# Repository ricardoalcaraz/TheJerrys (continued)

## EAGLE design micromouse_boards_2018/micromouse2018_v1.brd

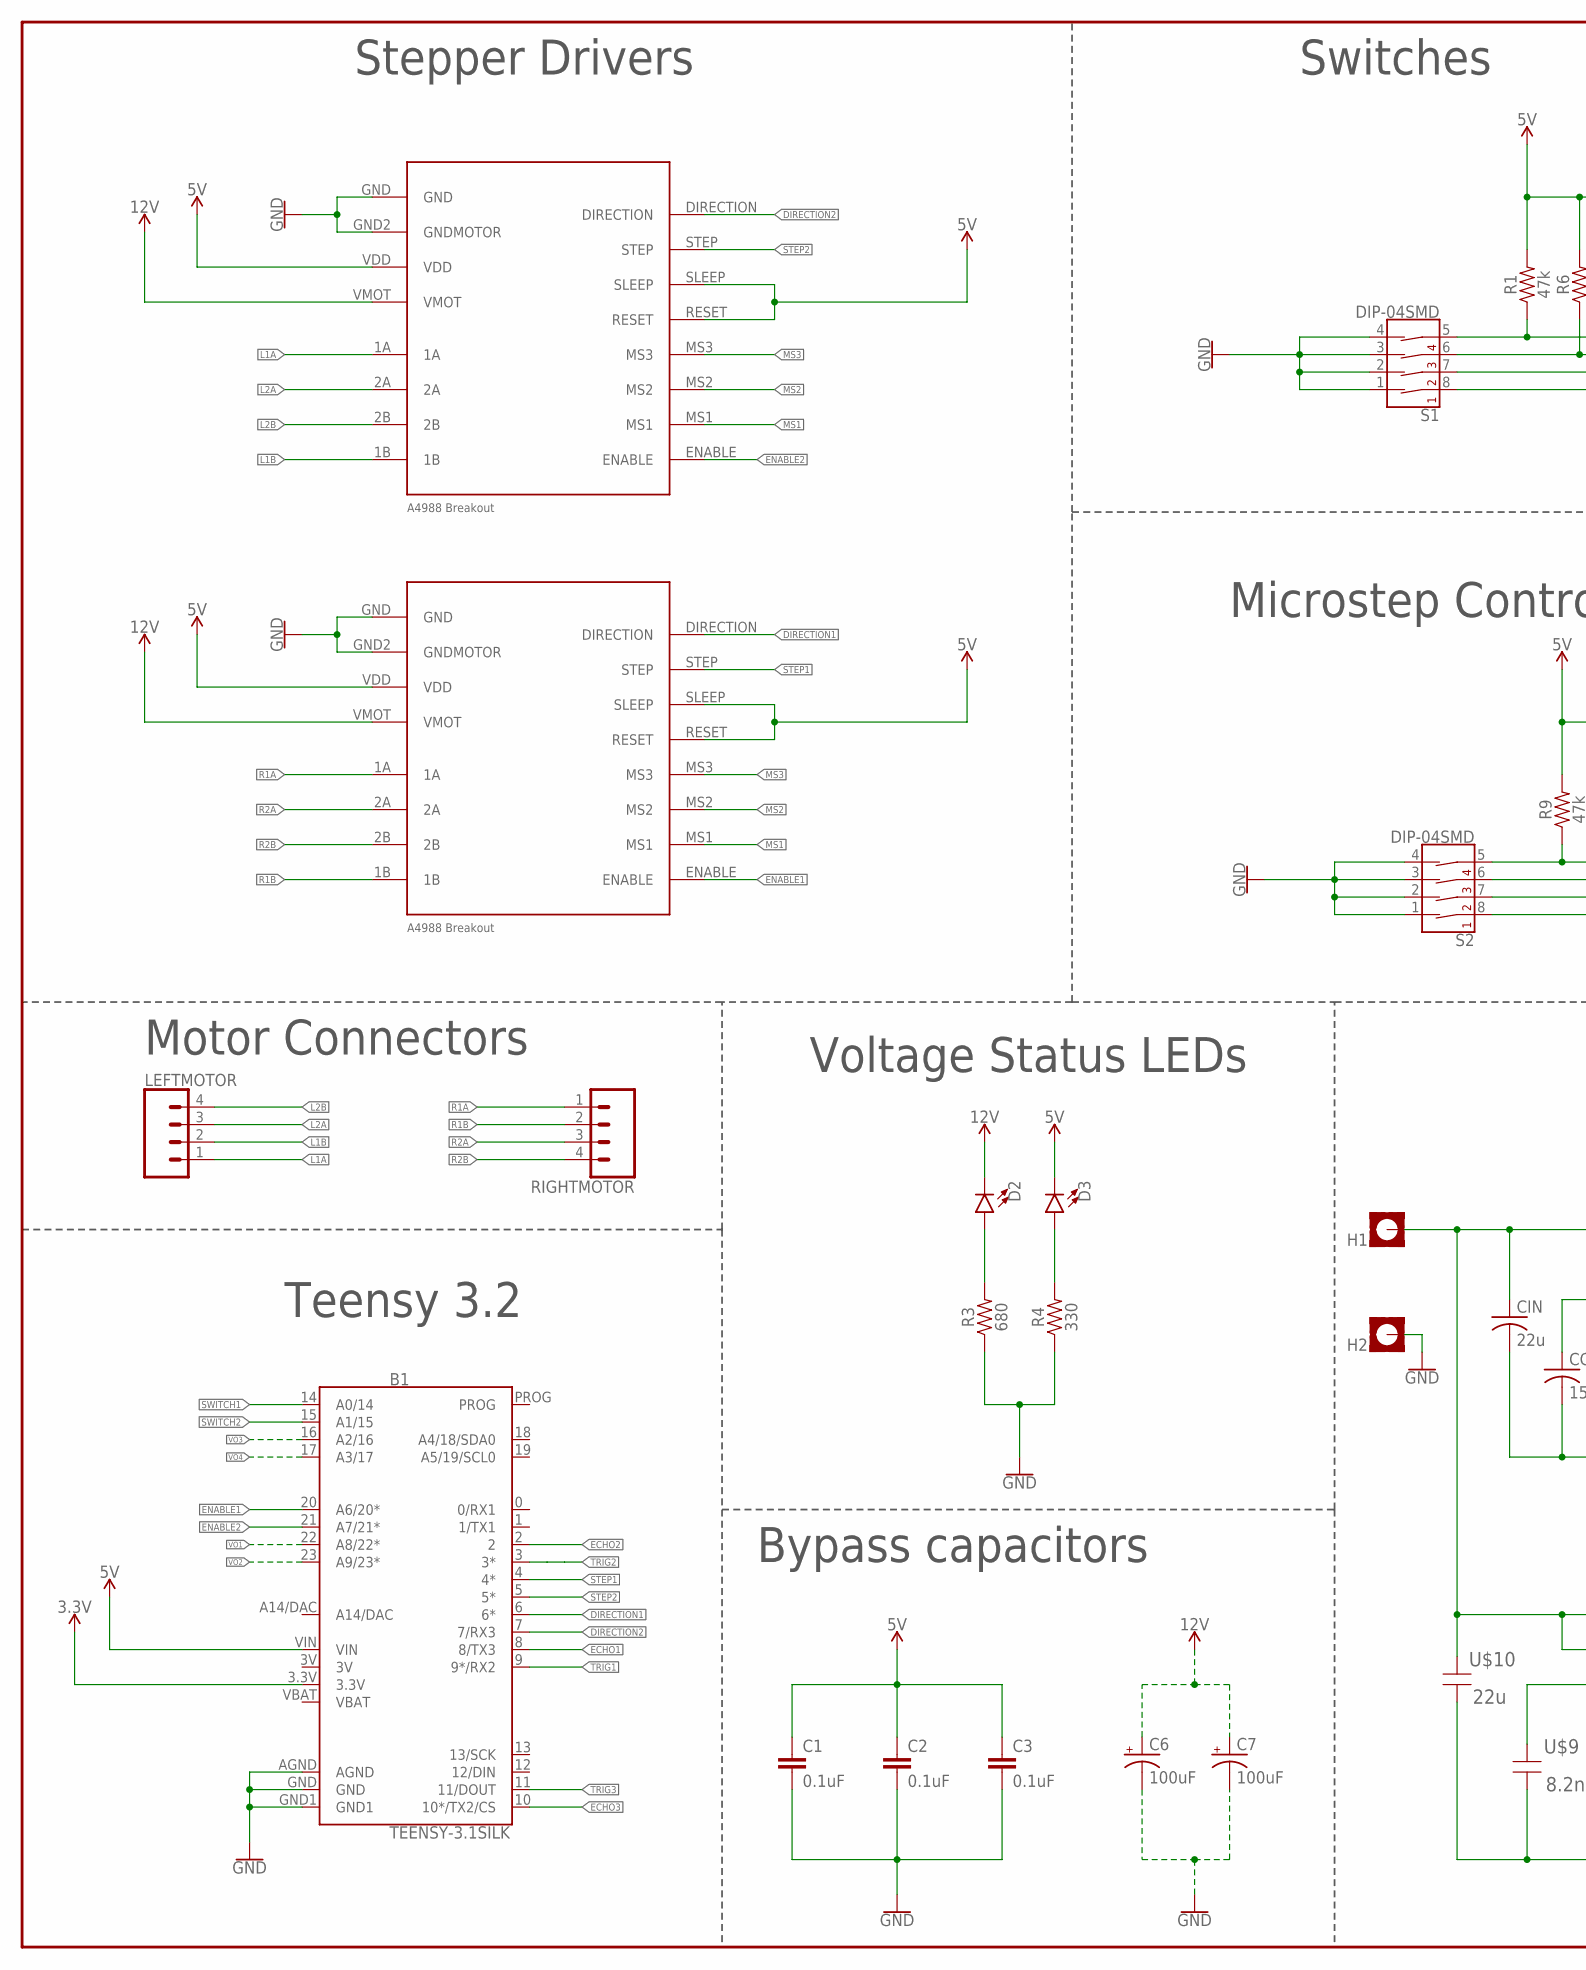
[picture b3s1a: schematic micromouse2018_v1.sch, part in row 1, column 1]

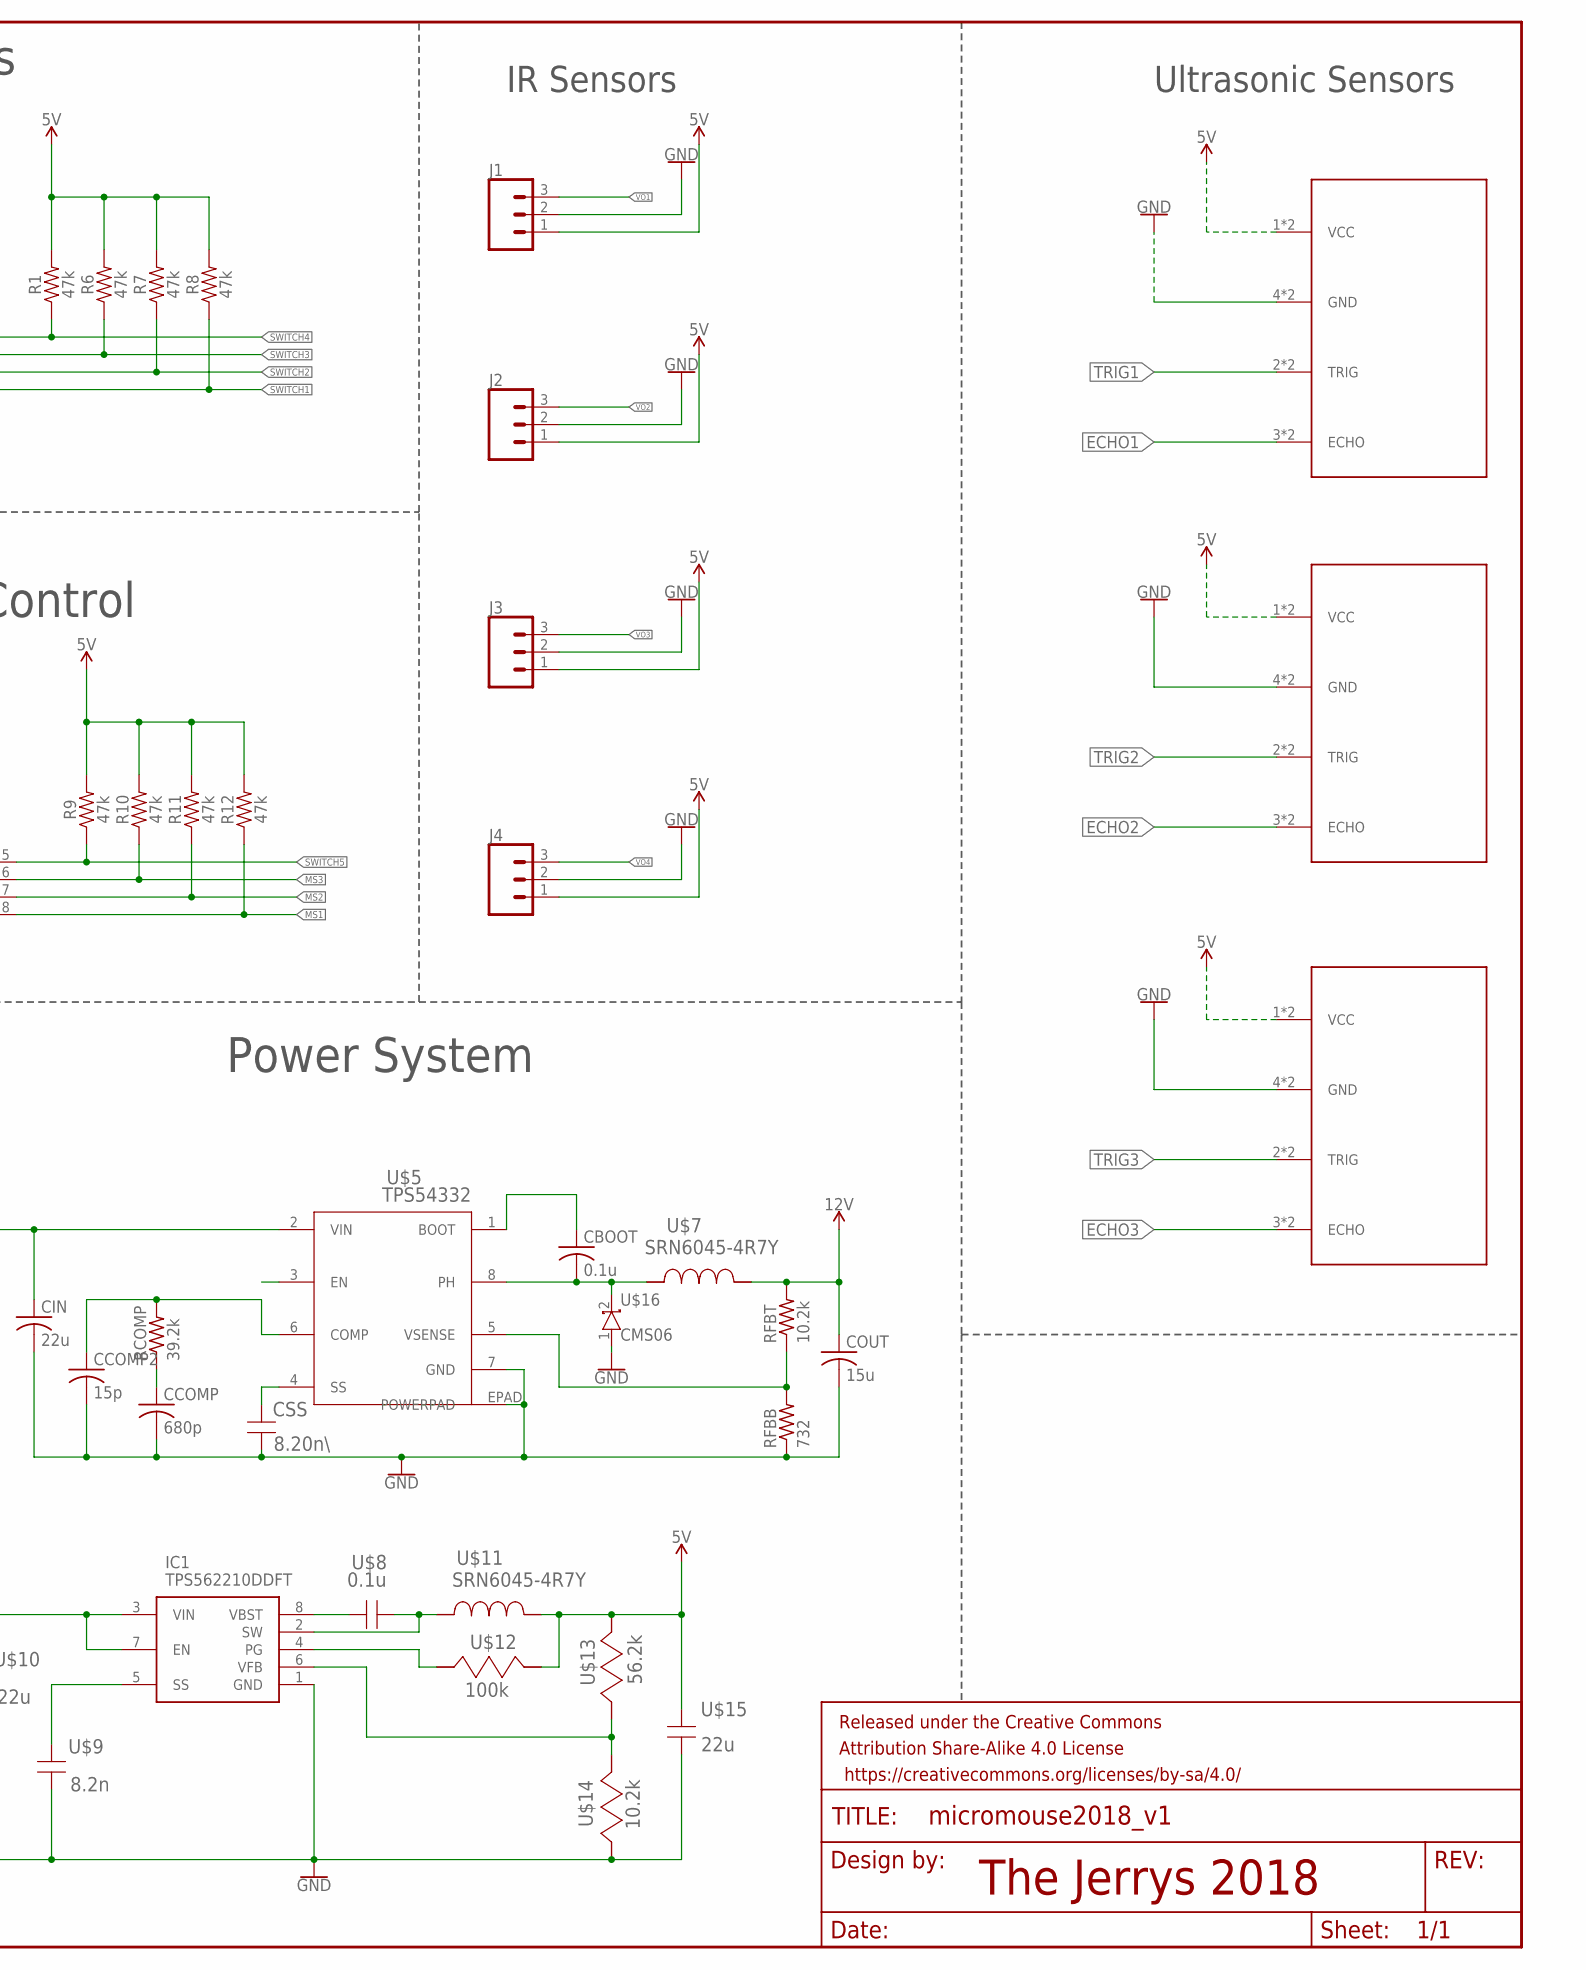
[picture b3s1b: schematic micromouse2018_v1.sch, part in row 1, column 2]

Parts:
B1: TEENSY-3.1SILK; TEENSY-3.1
C1, C2, C3: 0.1uF; 0603
C6, C7: 100uF; PANASONIC_D
CBOOT: 0.1u; C0805
CCOMP: 680p; C0805
CCOMP2: 15p; C0805
CIN: 22u; C1210
COUT: 15u; C0805
CSS: 8.20n\; 1206
D2, D3: LED0603; LED-0603
FRAME1: FRAME-LEDGER; CREATIVE_COMMONS
H1, H2: MOUNT-PAD-SQUARE2.8; 2,8-PAD-SQUARE
IC1: TPS562210DDFT; SOT65P280X110-8N
J1, J2, J3, J4: CONN_03JST-PTH-VERT; JST-3-PTH-VERT
LEFTMOTOR: CONN_04LONGPADS; 1X04_LONGPADS
R1, R6, R7, R8, R9, R10, R11, R12: 47k; 0603
R3: 680; 0603
R4: 330; 0603
RCOMP: 39.2k; R0805
RFBB: 732; R0805
RFBT: 10.2k; R0805
RIGHTMOTOR: CONN_04LONGPADS; 1X04_LONGPADS
S1, S2: DIP-04SMD; DIPSWITCH-04-SMD
U$1, U$2: A4988_BREAKOUT
U$3, U$4, U$6: ULTRASONIC; 1X04_SMD_VERTICAL_COMBO
U$5: TPS54332; DDA8_2P13X3-M
U$7, U$11: SRN6045-4R7Y; SRN6045
U$8: 0.1u; 0805
U$9: 8.2n; 1206
U$10: 22u; 1210
U$12: 100k; 0805
U$13: 56.2k; 0805
U$14: 10.2k; 0805
U$15: 22u; 1206_190
U$16: CMS06; SODFL4724X108N

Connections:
3.3V: B1.3.3V
3V: B1.3V
5V: B1.VIN, C1.1, C2.1, C3.1, D3.C, J1.1, J2.1, J3.1, J4.1, R1.2, R6.2, R7.2, R8.2, R9.2, R10.2, R11.2, R12.2, U$1.RESET, U$1.SLEEP, U$1.VDD, U$2.RESET, U$2.SLEEP, U$2.VDD, U$3.1 (VCC), U$3.1-2 (VCC), U$4.1 (VCC), U$4.1-2 (VCC), U$6.1 (VCC), U$6.1-2 (VCC), U$11.2, U$12.1, U$13.1, U$15.1
12V: C6.+, C7.+, COUT.1, D2.C, RFBT.2, U$1.VMOT, U$2.VMOT, U$7.2
BOOT: IC1.2 (SW), U$8.1, U$11.1
DIRECTION1: B1.6 (6*), U$2.DIRECTION
DIRECTION2: B1.7 (7/RX3), U$1.DIRECTION
ECHO1: B1.8 (8/TX3), U$3.3 (ECHO), U$3.3-2 (ECHO)
ECHO2: B1.2, U$4.3 (ECHO), U$4.3-2 (ECHO)
ECHO3: B1.10 (10*/TX2/CS), U$6.3 (ECHO), U$6.3-2 (ECHO)
ENABLE1: B1.20 (A6/20*), U$2.ENABLE
ENABLE2: B1.21 (A7/21*), U$1.ENABLE
GND: B1.AGND, B1.GND, B1.GND1, C1.2, C2.2, C3.2, C6.-, C7.-, CCOMP.2, CCOMP2.2, CIN.2, COUT.2, CSS.1, H2.B2,8, IC1.1 (GND), J1.2, J2.2, J3.2, J4.2, R3.1, R4.1, RFBB.1, S1.1 (1A), S1.2 (2A), S1.3 (3A), S1.4 (4A), S2.1 (1A), S2.2 (2A), S2.3 (3A), S2.4 (4A), U$1.GND, U$1.GND2 (GNDMOTOR), U$2.GND, U$2.GND2 (GNDMOTOR), U$3.4 (GND), U$3.4-2 (GND), U$4.4 (GND), U$4.4-2 (GND), U$5.7 (GND), U$5.EPAD (POWERPAD), U$6.4 (GND), U$6.4-2 (GND), U$9.2, U$10.2, U$14.2, U$15.2, U$16.1 (A)
L1A: LEFTMOTOR.1, U$1.1A
L1B: LEFTMOTOR.2, U$1.1B
L2A: LEFTMOTOR.3, U$1.2A
L2B: LEFTMOTOR.4, U$1.2B
MS1: R12.1, S2.8 (1B), U$1.MS1, U$2.MS1
MS2: R11.1, S2.7 (2B), U$1.MS2, U$2.MS2
MS3: R10.1, S2.6 (3B), U$1.MS3, U$2.MS3
unnamed: D2.A, R3.2
unnamed: D3.A, R4.2
unnamed: CSS.2, U$5.4 (SS)
unnamed: IC1.8 (VBST), U$8.2
unnamed: RFBB.2, RFBT.1, U$5.5 (VSENSE)
unnamed: CBOOT.1, U$5.1 (BOOT)
unnamed: CCOMP2.1, RCOMP.2, U$5.6 (COMP)
unnamed: CCOMP.1, RCOMP.1
unnamed: IC1.4 (PG), U$12.2
unnamed: IC1.6 (VFB), U$13.2, U$14.1
unnamed: IC1.5 (SS), U$9.1
PH: CBOOT.2, U$5.8 (PH), U$7.1, U$16.2 (K)
R1A: RIGHTMOTOR.1, U$2.1A
R1B: RIGHTMOTOR.2, U$2.1B
R2A: RIGHTMOTOR.3, U$2.2A
R2B: RIGHTMOTOR.4, U$2.2B
STEP1: B1.4 (4*), U$2.STEP
STEP2: B1.5 (5*), U$1.STEP
SWITCH1: B1.14 (A0/14), R8.1, S1.8 (1B)
SWITCH2: B1.15 (A1/15), R7.1, S1.7 (2B)
SWITCH3: R6.1, S1.6 (3B)
SWITCH4: R1.1, S1.5 (4B)
SWITCH5: R9.1, S2.5 (4B)
TRIG1: B1.9 (9*/RX2), U$3.2 (TRIG), U$3.2-2 (TRIG)
TRIG2: B1.3 (3*), U$4.2 (TRIG), U$4.2-2 (TRIG)
TRIG3: B1.11 (11/DOUT), U$6.2 (TRIG), U$6.2-2 (TRIG)
VBAT: B1.VBAT
VIN: CIN.1, H1.B2,8, IC1.3 (VIN), IC1.7 (EN), U$5.2 (VIN), U$10.1
VO1: B1.22 (A8/22*), J1.3
VO2: B1.23 (A9/23*), J2.3
VO3: B1.16 (A2/16), J3.3
VO4: B1.17 (A3/17), J4.3

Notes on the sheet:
Stepper Drivers
Teensy 3.2
Switches
Microstep Control
Motor Connectors
Voltage Status LEDs
Bypass capacitors
The Jerrys 2018
IR Sensors
Ultrasonic Sensors
Power System

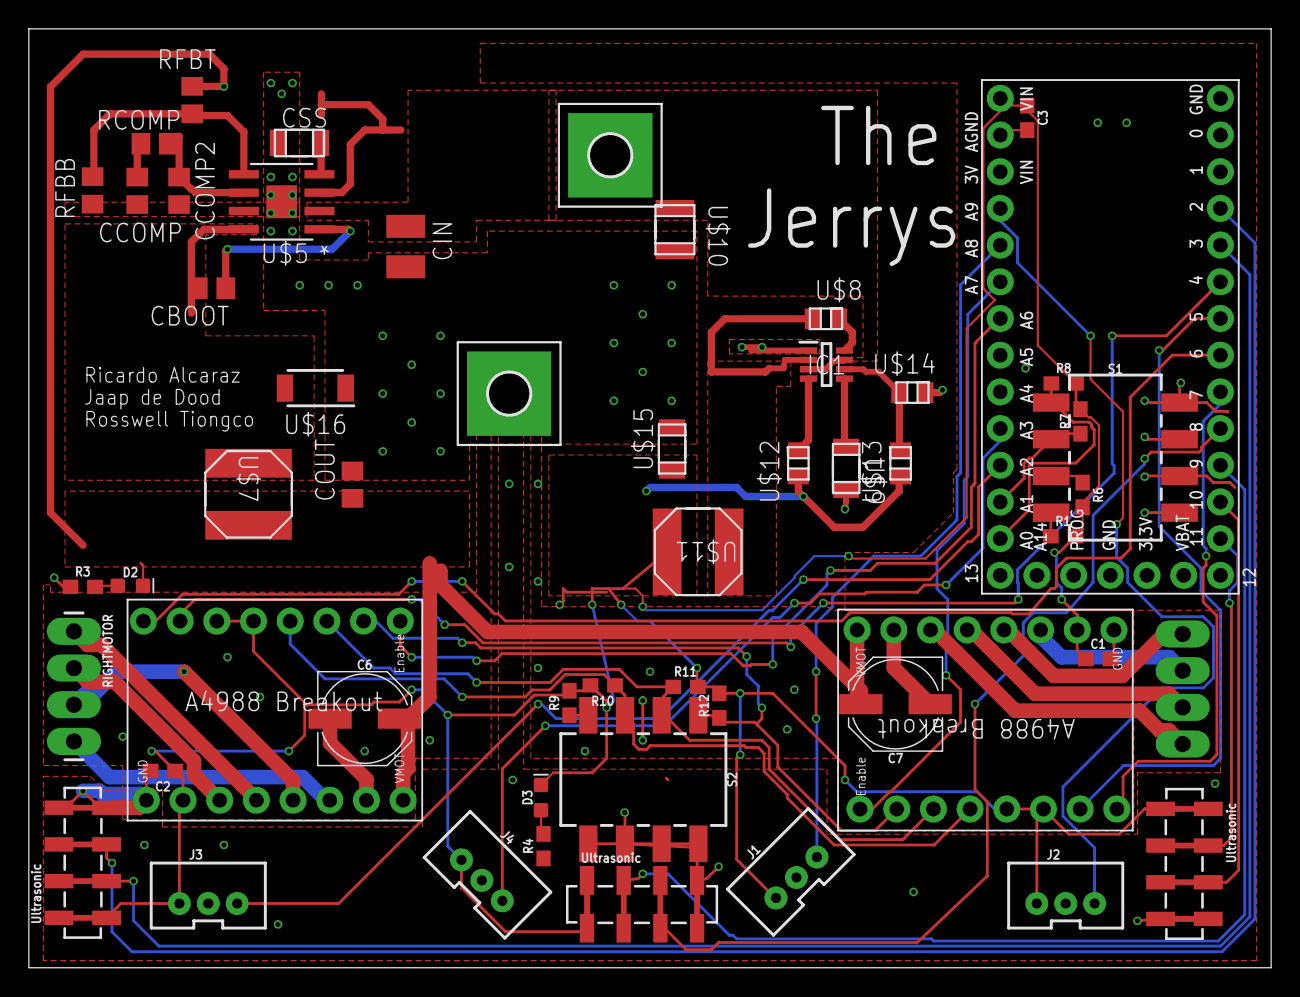
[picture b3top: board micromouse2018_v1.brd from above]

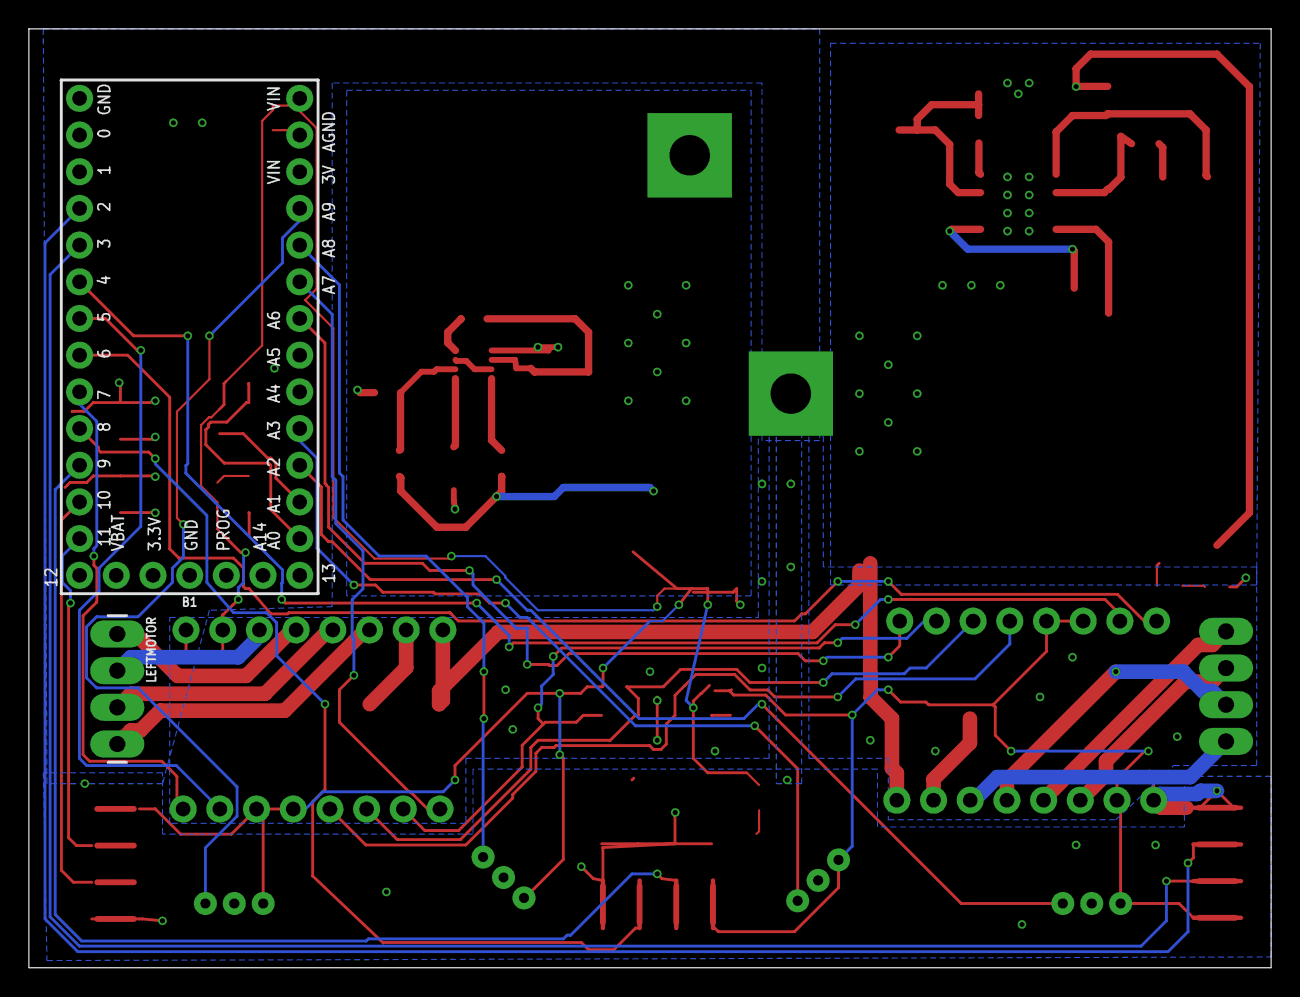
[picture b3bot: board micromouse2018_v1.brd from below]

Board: 2 copper layers, 86.0 x 65.0 mm, 55 parts (2 on the bottom side), 49 nets.

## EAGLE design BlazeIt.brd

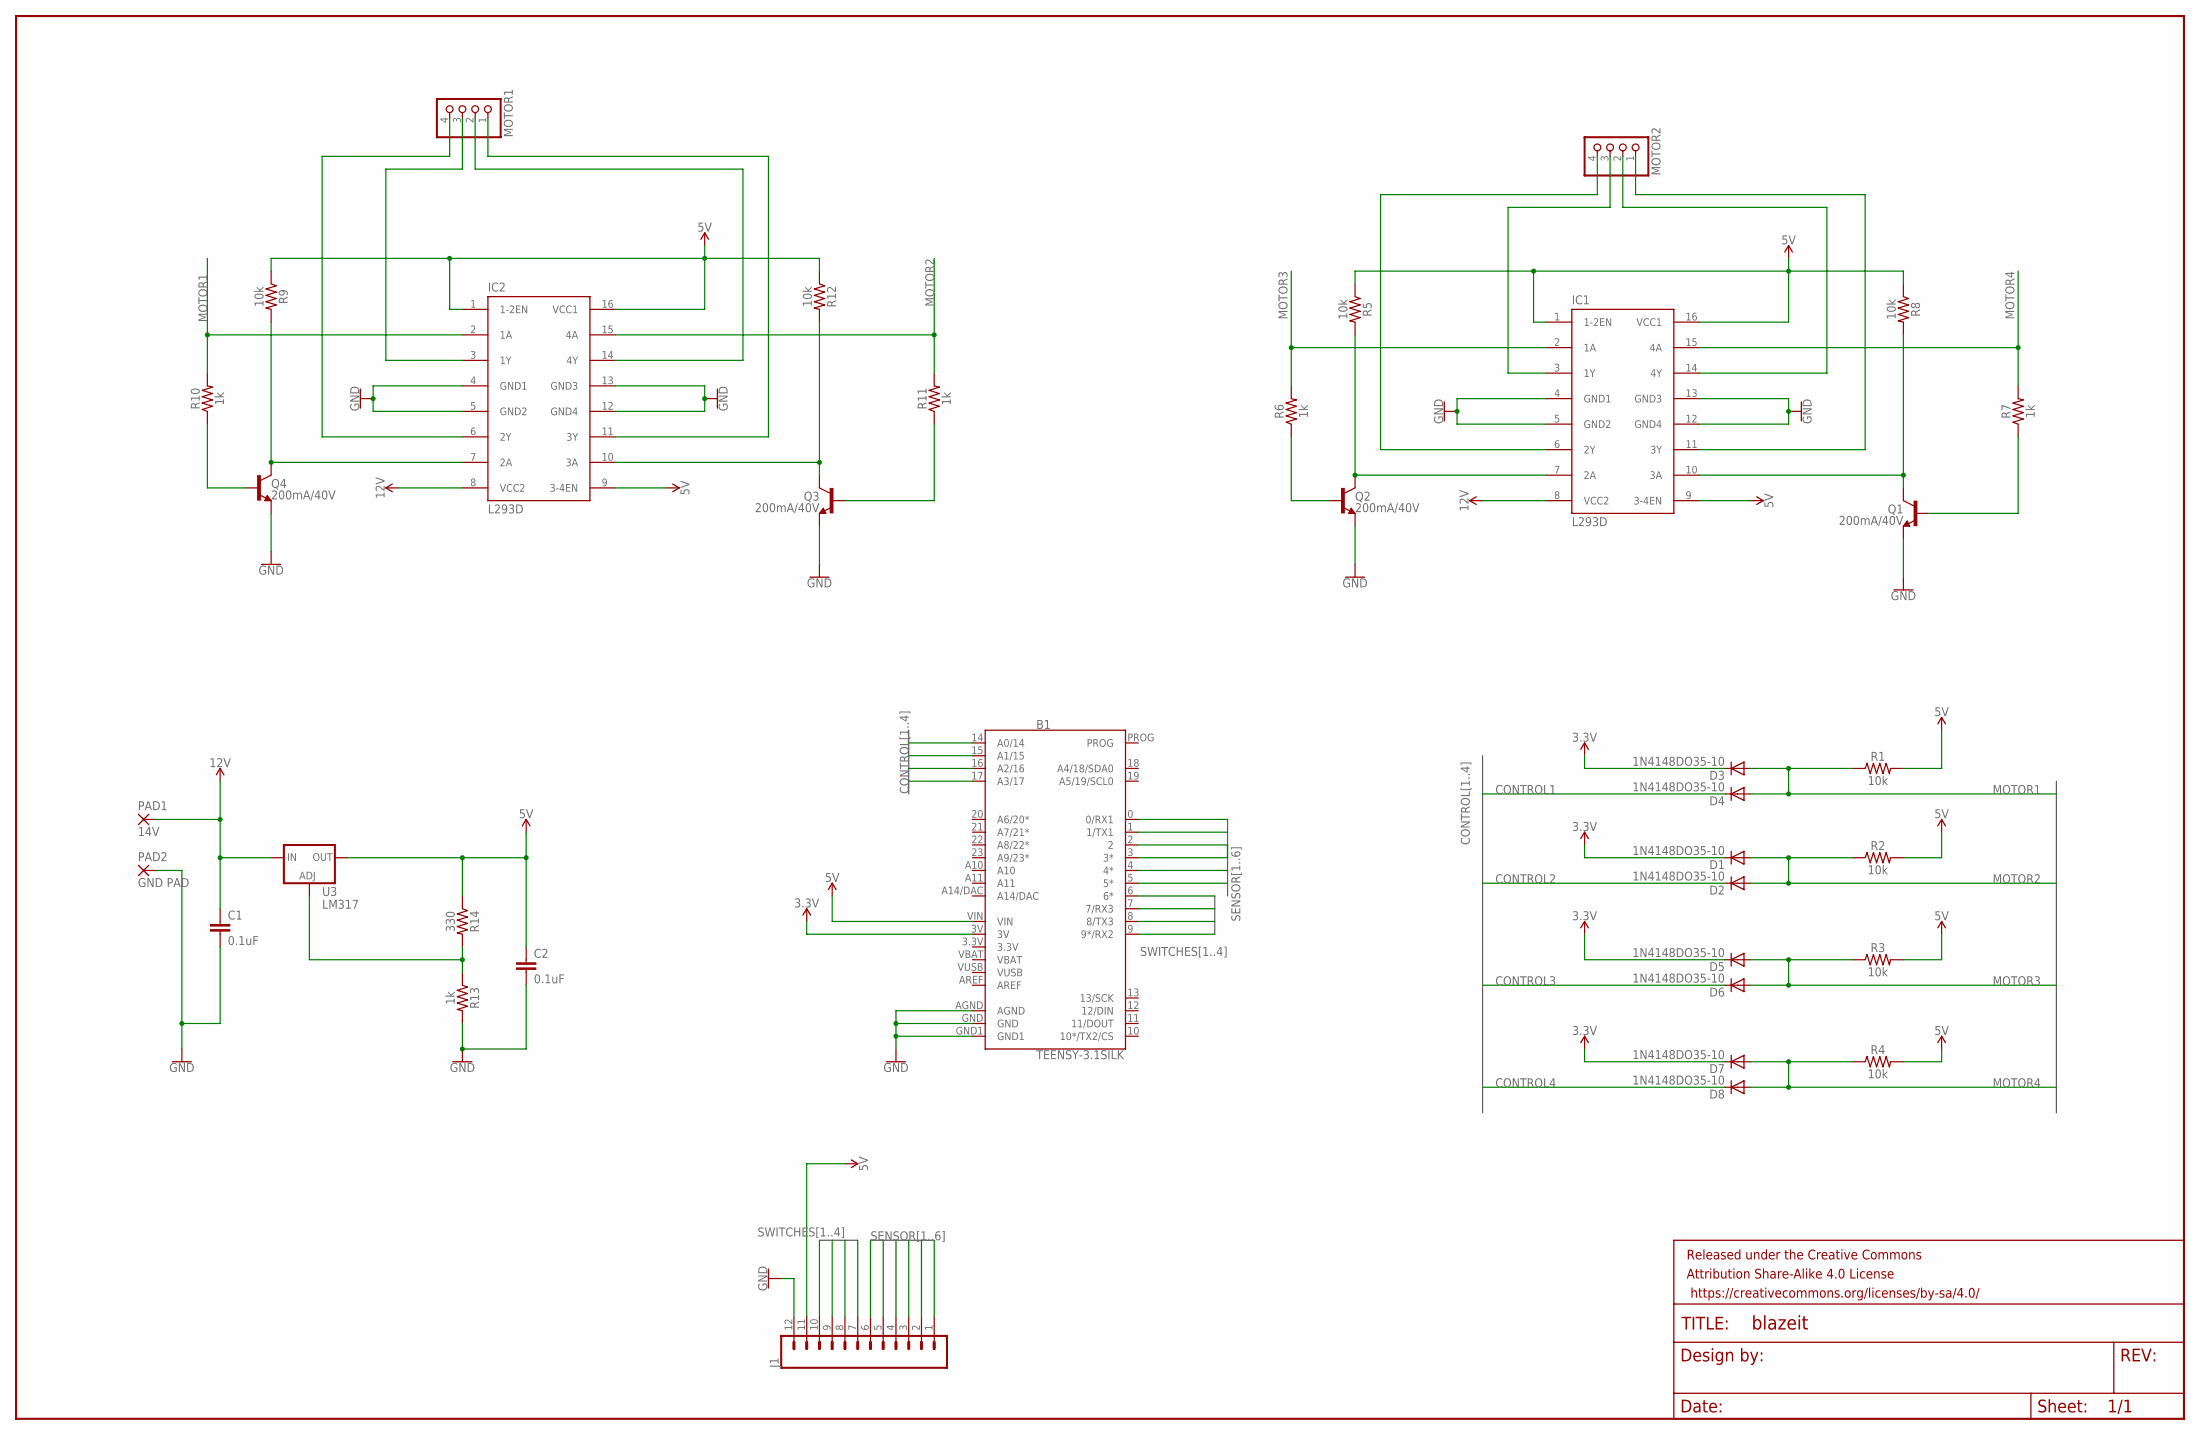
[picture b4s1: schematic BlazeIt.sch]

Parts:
B1: TEENSY-3.1SILK; TEENSY-3.1
C1, C2: 0.1uF; CAP-PTH-SMALL-KIT
D1, D2, D3, D4, D5, D6, D7, D8: 1N4148DO35-10; DO35-10
FRAME1: FRAME-LEDGER; CREATIVE_COMMONS
IC1, IC2: L293D; DIL16
J1: CONN_12; 1X12
MOTOR1, MOTOR2: PINHD-1X4; 1X04
PAD1: 14V; SMD2,54-5,08
PAD2: GND PAD; SMD2,54-5,08
Q1, Q2, Q3, Q4: 200mA/40V; TO-92
R1, R2, R3, R4, R5, R8, R9, R12: 10k; AXIAL-0.3
R6, R7, R10, R11, R13: 1k; AXIAL-0.3
R14: 330; AXIAL-0.3
U3: LM317; TO220-ADJ

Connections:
3.3V: B1.3.3V, B1.3V, D1.C, D3.C, D5.C, D7.C
5V: B1.VIN, C2.1, IC1.1 (1-2EN), IC1.9 (3-4EN), IC1.16 (VCC1), IC2.1 (1-2EN), IC2.9 (3-4EN), IC2.16 (VCC1), J1.11, R1.P$2 (2), R2.P$2 (2), R3.P$2 (2), R4.P$2 (2), R5.P$1 (1), R8.P$1 (1), R9.P$1 (1), R12.P$1 (1), R14.P$1 (1), U3.OUT
12V: C1.1, IC1.8 (VCC2), IC2.8 (VCC2), PAD1.1, U3.IN
CONTROL1: B1.17 (A3/17), D4.C
CONTROL2: B1.16 (A2/16), D2.C
CONTROL3: B1.15 (A1/15), D6.C
CONTROL4: B1.14 (A0/14), D8.C
GND: B1.AGND, B1.GND, B1.GND1, C1.2, C2.2, IC1.4 (GND1), IC1.5 (GND2), IC1.12 (GND4), IC1.13 (GND3), IC2.4 (GND1), IC2.5 (GND2), IC2.12 (GND4), IC2.13 (GND3), J1.12, PAD2.1, Q1.1 (E), Q2.1 (E), Q3.1 (E), Q4.1 (E), R13.P$2 (2)
MOTOR1: D3.A, D4.A, IC2.2 (1A), R1.P$1 (1), R10.P$2 (2)
MOTOR2: D1.A, D2.A, IC2.15 (4A), R2.P$1 (1), R11.P$2 (2)
MOTOR3: D5.A, D6.A, IC1.2 (1A), R3.P$1 (1), R6.P$2 (2)
MOTOR4: D7.A, D8.A, IC1.15 (4A), R4.P$1 (1), R7.P$2 (2)
unnamed: IC2.3 (1Y), MOTOR1.3
unnamed: IC1.3 (1Y), MOTOR2.3
unnamed: IC2.11 (3Y), MOTOR1.1
unnamed: IC1.6 (2Y), MOTOR2.4
unnamed: IC1.11 (3Y), MOTOR2.1
unnamed: R13.P$1 (1), R14.P$2 (2), U3.ADJ
unnamed: Q2.2 (B), R6.P$1 (1)
unnamed: IC1.7 (2A), Q2.3 (C), R5.P$2 (2)
unnamed: IC1.14 (4Y), MOTOR2.2
unnamed: IC1.10 (3A), Q1.3 (C), R8.P$2 (2)
unnamed: Q1.2 (B), R7.P$1 (1)
unnamed: Q4.2 (B), R10.P$1 (1)
unnamed: IC2.7 (2A), Q4.3 (C), R9.P$2 (2)
unnamed: IC2.6 (2Y), MOTOR1.4
unnamed: IC2.14 (4Y), MOTOR1.2
unnamed: IC2.10 (3A), Q3.3 (C), R12.P$2 (2)
unnamed: Q3.2 (B), R11.P$1 (1)
SENSOR1: B1.0 (0/RX1), J1.1
SENSOR2: B1.1 (1/TX1), J1.2
SENSOR3: B1.2, J1.3
SENSOR4: B1.3 (3*), J1.4
SENSOR5: B1.4 (4*), J1.5
SENSOR6: B1.5 (5*), J1.6
SWITCHES1: B1.6 (6*), J1.7
SWITCHES2: B1.7 (7/RX3), J1.8
SWITCHES3: B1.8 (8/TX3), J1.9
SWITCHES4: B1.9 (9*/RX2), J1.10
VBAT: B1.VBAT
VUSB: B1.VUSB

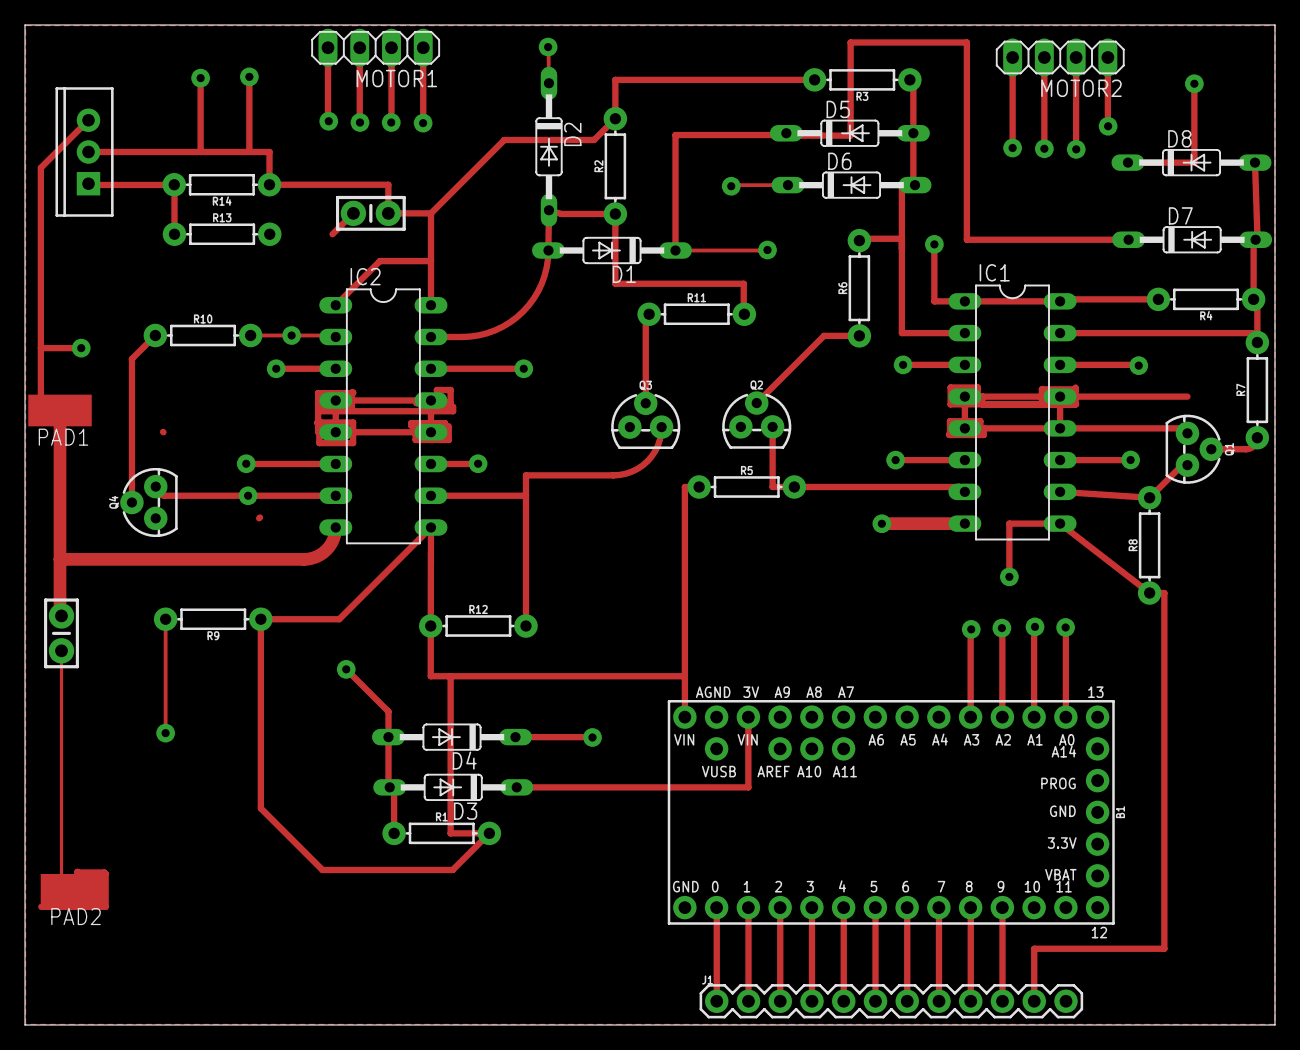
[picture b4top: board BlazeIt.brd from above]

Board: 2 copper layers, 100.0 x 80.0 mm, 38 parts (0 on the bottom side), 39 nets.

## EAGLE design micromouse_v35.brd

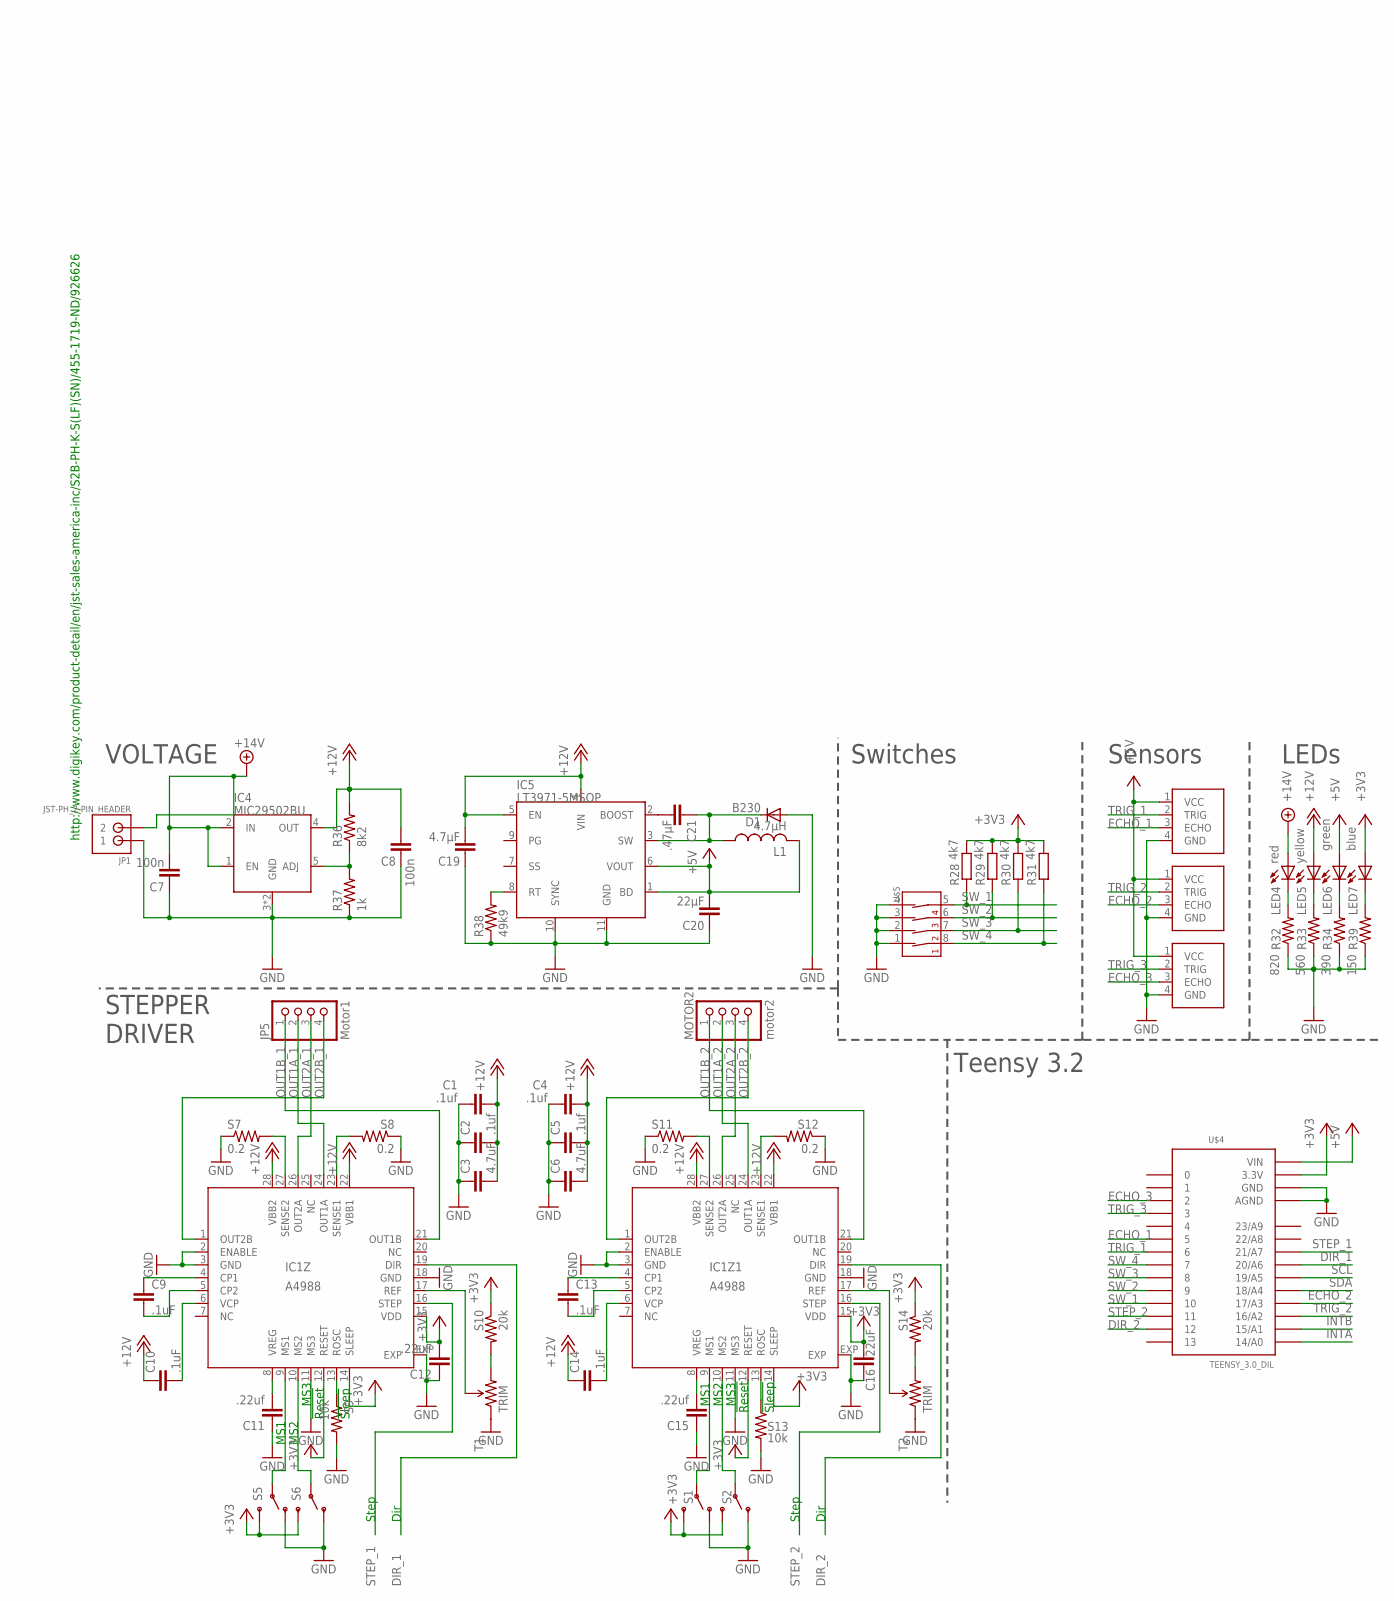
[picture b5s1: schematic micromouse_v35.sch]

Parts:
C1, C2, C4, C5: .1uf; C0603
C3, C6: 4.7uF; 1206
C7, C8: 100n; C0603
C9, C10, C13, C14: .1uF; C0603
C11, C15: .22uf; C0603
C12, C16: .22uF; C0603
C19: 4.7µF; C0603
C20: 22µF; C0805
C21: .47µF; C0603
D1: B230; DO-214AC
IC1Z, IC1Z1: A4988; QFN28ET
IC4: MIC29502BU; TO-263-5
IC5: LT3971-5MSOP; MSOP-10
JP1: JST-PH_2-PIN_HEADER; JST_B2B-PH_HEADER
JP5: Motor1; 1X04
L1: 4.7µH; L1812
LED4: red; SML0603
LED5: yellow; SML0603
LED6: green; SML0603
LED7: blue; SML0603
MOTOR2: motor2; 1X04
R28, R29, R30, R31: 4k7; R0603
R32: 820; R0603
R33: 560; R0603
R34: 390; R0603
R36: 8k2; R0603
R37: 1k; R0603
R38: 49k9; R0603
R39: 150; R0603
S1, S2, S5, S6: SWITCH-SPDT-SMD-A; SWITCH-SPST-SMD-A
S7, S8, S11, S12: 0.2; R0603
S9, S13: 10k; R0603
S10, S14: 20k; R0603
SENSOR1, SENSOR2, SENSOR3: HC-SR04SMD; HC-SR04_SMD
T1, T2: TRIM; TRIMPOT-3MM
U$4: TEENSY_3.0_DIL; TEENSY3-DIL
U$5: 4-POS-DIP; 4-POS-DIP-SMD

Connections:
+3V3: C12.2, C16.2, IC1Z.12 (RESET), IC1Z.14 (SLEEP), IC1Z.15 (VDD), IC1Z1.12 (RESET), IC1Z1.14 (SLEEP), IC1Z1.15 (VDD), LED7.A, R28.2, R29.2, R30.2, R31.2, S1.3 (S), S2.3 (S), S5.3 (S), S6.3 (S), S10.1, S14.1, U$4.3.3V
+5V: C20.2, IC5.1 (BD), IC5.6 (VOUT), L1.2, LED6.A, SENSOR1.1 (VCC), SENSOR2.1 (VCC), SENSOR3.1 (VCC), U$4.VIN
+12V: C1.2, C2.2, C3.2, C4.2, C5.2, C6.2, C8.2, C10.1, C14.1, C19.2, IC1Z.22 (VBB1), IC1Z.28 (VBB2), IC1Z1.22 (VBB1), IC1Z1.28 (VBB2), IC4.4 (OUT), IC5.4 (VIN), IC5.5 (EN), LED5.A, R36.2
+14V: C7.2, IC4.1 (EN), IC4.2 (IN), JP1.P2 (2), LED4.A
DIR_1: IC1Z.19 (DIR), U$4.20/A6
DIR_2: IC1Z1.19 (DIR), U$4.12
ECHO_1: SENSOR1.3 (ECHO), U$4.5
ECHO_2: SENSOR2.3 (ECHO), U$4.17/A3
ECHO_3: SENSOR3.3 (ECHO), U$4.2
GND: C1.1, C2.1, C3.1, C4.1, C5.1, C6.1, C7.1, C8.1, C11.1, C12.1, C15.1, C16.1, C19.1, C20.1, D1.A, IC1Z.2 (ENABLE), IC1Z.3 (GND), IC1Z.11 (MS3), IC1Z.18 (GND), IC1Z.EXP, IC1Z1.2 (ENABLE), IC1Z1.3 (GND), IC1Z1.11 (MS3), IC1Z1.18 (GND), IC1Z1.EXP, IC4.3 (GND), IC4.6 (GND), IC5.10 (SYNC), IC5.11 (GND), JP1.P1 (1), R32.1, R33.1, R34.1, R37.1, R38.1, R39.1, S1.1 (O), S2.1 (O), S5.1 (O), S6.1 (O), S7.1, S8.1, S9.2, S11.1, S12.1, S13.2, SENSOR1.4 (GND), SENSOR2.4 (GND), SENSOR3.4 (GND), T1.1 (CCW), T2.1 (CCW), U$4.AGND, U$4.GND, U$5.1 (1A), U$5.2 (2A), U$5.3 (3A), U$5.4 (4A)
INTA: U$4.14/A0
INTB: U$4.15/A1
unnamed: LED4.C, R32.2
unnamed: LED5.C, R33.2
unnamed: LED6.C, R34.2
unnamed: IC4.5 (ADJ), R36.1, R37.2
unnamed: IC5.8 (RT), R38.2
unnamed: C21.2, IC5.2 (BOOST)
unnamed: C21.1, D1.C, IC5.3 (SW), L1.1
unnamed: LED7.C, R39.2
OUT1A_1: IC1Z.24 (OUT1A), JP5.2
OUT1A_2: IC1Z1.24 (OUT1A), MOTOR2.2
OUT1B_1: IC1Z.21 (OUT1B), JP5.1
OUT1B_2: IC1Z1.21 (OUT1B), MOTOR2.1
OUT2A_1: IC1Z.26 (OUT2A), JP5.3
OUT2A_2: IC1Z1.26 (OUT2A), MOTOR2.3
OUT2B_1: IC1Z.1 (OUT2B), JP5.4
OUT2B_2: IC1Z1.1 (OUT2B), MOTOR2.4
SCL: U$4.19/A5
SDA: U$4.18/A4
STEP_1: IC1Z.16 (STEP), U$4.21/A7
STEP_2: IC1Z1.16 (STEP), U$4.11
SW_1: R28.1, U$4.10, U$5.5 (4B)
SW_2: R29.1, U$4.9, U$5.6 (3B)
SW_3: R30.1, U$4.8, U$5.7 (2B)
SW_4: R31.1, U$4.7, U$5.8 (1B)
TRIG_1: SENSOR1.2 (TRIG), U$4.6
TRIG_2: SENSOR2.2 (TRIG), U$4.16/A2
TRIG_3: SENSOR3.2 (TRIG), U$4.3
ZCP1: C9.1, IC1Z.4 (CP1)
ZCP2: C9.2, IC1Z.5 (CP2)
ZCP3: C13.1, IC1Z1.4 (CP1)
ZCP4: C13.2, IC1Z1.5 (CP2)
ZMS1: IC1Z.9 (MS1), S5.2
ZMS2: IC1Z.10 (MS2), S6.2
ZMS3: IC1Z1.9 (MS1), S1.2
ZMS4: IC1Z1.10 (MS2), S2.2
ZREF: IC1Z.17 (REF), T1.2 (WIPER)
ZREF1: IC1Z1.17 (REF), T2.2 (WIPER)
ZREF2: S10.2, T1.3 (CW)
ZREF3: S14.2, T2.3 (CW)
ZROSC: IC1Z.13 (ROSC), S9.1
ZROSC1: IC1Z1.13 (ROSC), S13.1
ZSENSE1: IC1Z.23 (SENSE1), S8.2
ZSENSE2: IC1Z.27 (SENSE2), S7.2
ZSENSE3: IC1Z1.27 (SENSE2), S11.2
ZSENSE4: IC1Z1.23 (SENSE1), S12.2
ZVCP: C10.2, IC1Z.6 (VCP)
ZVCP1: C14.2, IC1Z1.6 (VCP)
ZVREG: C11.2, IC1Z.8 (VREG)
ZVREG1: C15.2, IC1Z1.8 (VREG)

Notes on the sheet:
MS3
!Reset
!Sleep
MS1
MS2
Step
Dir
VOLTAGE
STEPPER DRIVER
LEDs
Teensy 3.2
Sensors
Switches
http://www.digikey.com/product-detail/en/jst-sales-america-inc/S2B-PH-K-S(LF)(SN)/455-1719-ND/926626
